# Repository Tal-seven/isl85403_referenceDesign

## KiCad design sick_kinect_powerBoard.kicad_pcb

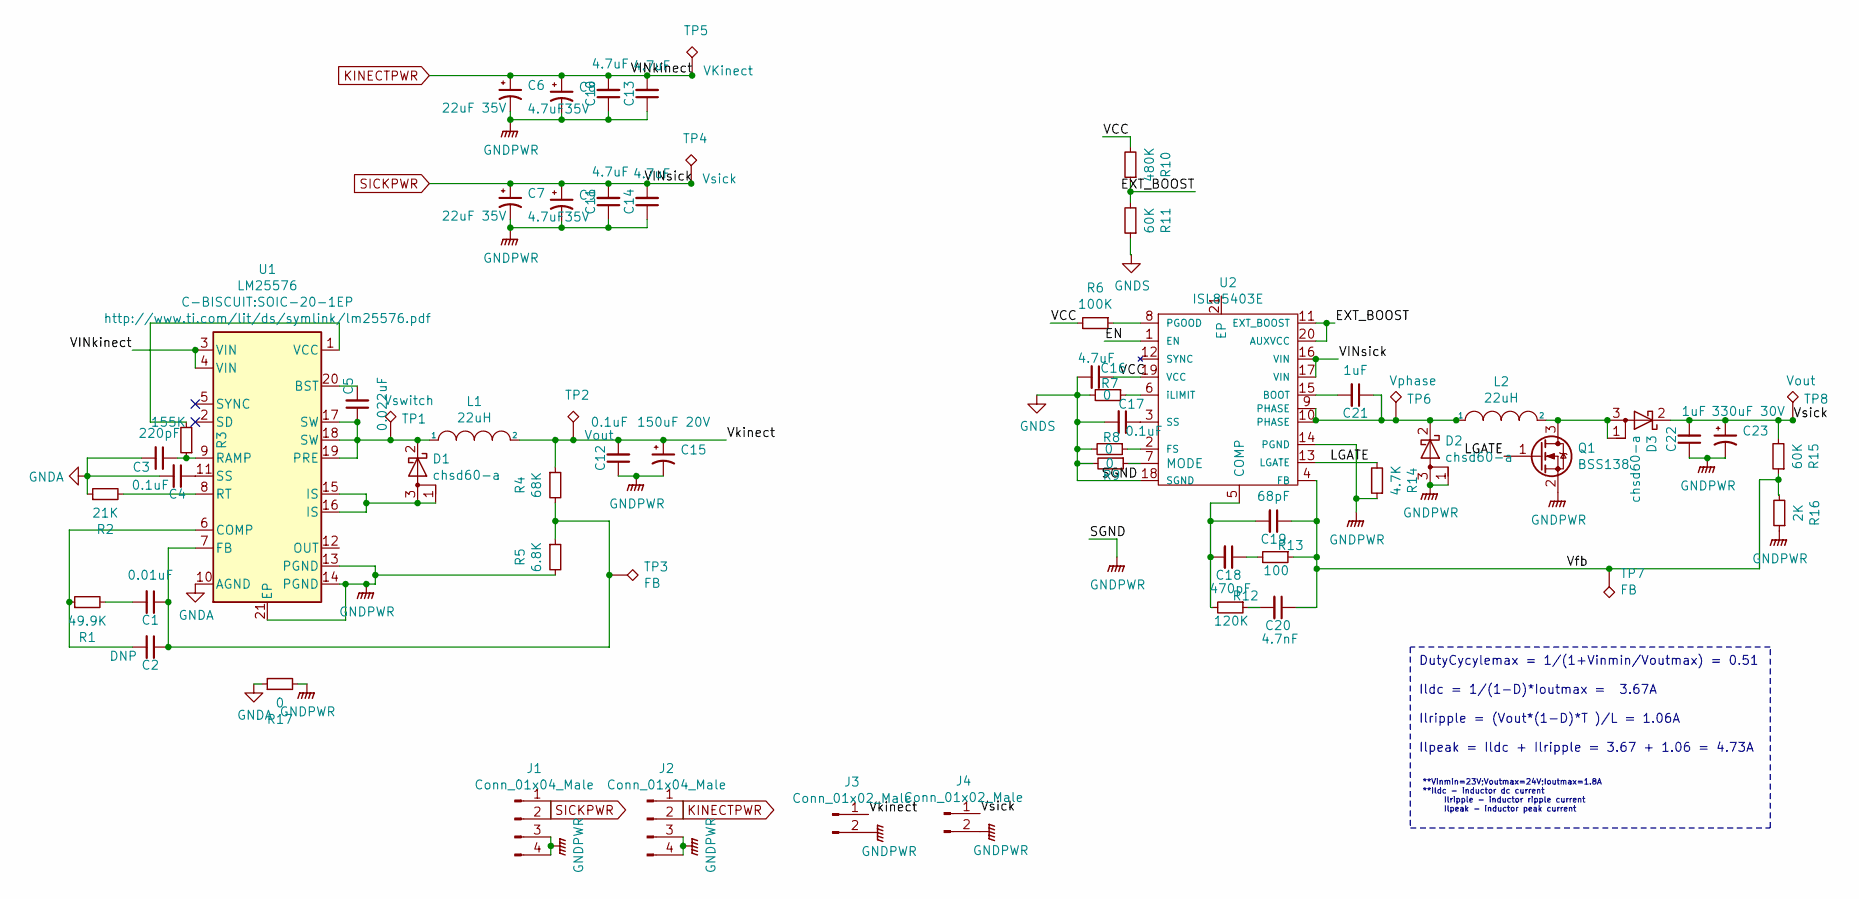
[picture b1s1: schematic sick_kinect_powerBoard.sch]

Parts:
C1: 0.01uF; C_0603_1608Metric_Pad1.05x0.95mm_HandSolder
C2: DNP; C_0603_1608Metric_Pad1.05x0.95mm_HandSolder
C3: 220pF; C_0603_1608Metric_Pad1.05x0.95mm_HandSolder
C4, C12, C17: 0.1uF; C_0603_1608Metric_Pad1.05x0.95mm_HandSolder
C5: 0.022uF; C_0603_1608Metric_Pad1.05x0.95mm_HandSolder
C6, C7: 22uF 35V; CP_Elec_6.3x5.3
C8, C9: 4.7uF35V; CP_Elec_4x5.7
C10, C11, C13, C14, C16: 4.7uF; C_0603_1608Metric_Pad1.05x0.95mm_HandSolder
C15: 150uF 20V; CP_Elec_6.3x7.7
C18: 470pF; C_0603_1608Metric_Pad1.05x0.95mm_HandSolder
C19: 68pF; C_0603_1608Metric_Pad1.05x0.95mm_HandSolder
C20: 4.7nF; C_0603_1608Metric_Pad1.05x0.95mm_HandSolder
C21, C22: 1uF; C_0603_1608Metric_Pad1.05x0.95mm_HandSolder
C23: 330uF 30V; CP_Elec_10x10
D1, D2, D3: chsd60-a; TO-252-2
J1, J2: Conn_01x04_Male; Molex_MegaFit_2x02x5.70mm_Straight
J3, J4: Conn_01x02_Male; Molex_Mega-Fit_76829-0102_2x01_P5.70mm_Vertical
L1, L2: 22uH; L_12x12mm_H4.5mm
Q1: BSS138; SOT-23
R1: 49.9K; R_0603_1608Metric_Pad1.05x0.95mm_HandSolder
R2: 21K; R_0603_1608Metric_Pad1.05x0.95mm_HandSolder
R3: 155K; R_0603_1608Metric_Pad1.05x0.95mm_HandSolder
R4: 68K; R_0603_1608Metric_Pad1.05x0.95mm_HandSolder
R5: 6.8K; R_0603_1608Metric_Pad1.05x0.95mm_HandSolder
R6: 100K; R_0603_1608Metric_Pad1.05x0.95mm_HandSolder
R7, R8, R9, R17: 0; R_0603_1608Metric_Pad1.05x0.95mm_HandSolder
R10: 480K; R_0603_1608Metric_Pad1.05x0.95mm_HandSolder
R11, R15: 60K; R_0603_1608Metric_Pad1.05x0.95mm_HandSolder
R12: 120K; R_0603_1608Metric_Pad1.05x0.95mm_HandSolder
R13: 100; R_0603_1608Metric_Pad1.05x0.95mm_HandSolder
R14: 4.7K; R_0603_1608Metric_Pad1.05x0.95mm_HandSolder
R16: 2K; R_0603_1608Metric_Pad1.05x0.95mm_HandSolder
TP1: Vswitch; TestPoint_Pad_1.5x1.5mm
TP2, TP8: Vout; TestPoint_Pad_1.5x1.5mm
TP3, TP7: FB; TestPoint_Pad_1.5x1.5mm
TP4: Vsick; TestPoint_Pad_1.5x1.5mm
TP5: VKinect; TestPoint_Pad_1.5x1.5mm
TP6: Vphase; TestPoint_Pad_1.5x1.5mm
U1: LM25576; SOIC-20-1EP
U2: ISL85403E; QFN-20-1EP_4x4mm_P0.5mm_EP2.7x2.7mm_ThermalVias

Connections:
/EN: U2.1 (EN)
/EXT_BOOST: R10.1, R11.2, U2.11 (EXT_BOOST), U2.20 (AUXVCC)
/LGATE: Q1.1 (G), R14.2, U2.13 (LGATE)
/VCC: C16.1, R6.2, R10.2, U2.19 (VCC)
/Vfb: C19.1, C20.1, R13.1, R15.1, R16.2, TP7.1, U2.4 (FB)
/Vkinect: C12.2, C15.1, J3.1, L1.2, R4.1, TP2.1
/Vsick: C22.2, C23.1, D3.2 (K), J4.1, R15.2, TP8.1
GNDA: C3.2, C4.2, R2.1, R17.1, U1.10 (AGND)
GNDPWR: C6.2, C7.2, C8.2, C9.2, C10.1, C11.1, C12.1, C13.1, C14.1, C15.2, C16.2, C17.2, C22.1, C23.2, D2.1 (A), D2.3 (A), J1.3, J1.4, J2.3, J2.4, J3.2, J4.2, Q1.2 (S), R5.2, R7.2, R8.2, R9.2, R11.1, R14.1, R16.1, R17.2, U1.13 (PGND), U1.14 (PGND), U1.21 (EP), U2.14 (PGND), U2.18 (SGND)
KINECTPWR: C6.1, C8.1, C10.2, C13.2, J2.1, J2.2, TP5.1, U1.3 (VIN), U1.4 (VIN)
unnamed: C1.1, C2.1, R4.2, R5.1, TP3.1, U1.7 (FB)
unnamed: C1.2, R1.2
unnamed: C2.2, R1.1, U1.6 (COMP)
unnamed: C3.1, R3.1, U1.9 (RAMP)
unnamed: C4.1, U1.11 (SS)
unnamed: C5.1, D1.2 (K), L1.1, TP1.1, U1.17 (SW), U1.18 (SW), U1.19 (PRE)
unnamed: C5.2, U1.20 (BST)
unnamed: C17.1, U2.3 (SS)
unnamed: C18.1, R13.2
unnamed: C18.2, C19.2, R12.2, U2.5 (COMP)
unnamed: C20.2, R12.1
unnamed: C21.1, D2.2 (K), L2.1, TP6.1, U2.9 (PHASE), U2.10 (PHASE)
unnamed: C21.2, U2.15 (BOOT)
unnamed: D1.1 (A), D1.3 (A), U1.15 (IS), U1.16 (IS)
unnamed: D3.1 (A), D3.3 (A), L2.2, Q1.3 (D)
unnamed: R2.2, U1.8 (RT)
unnamed: R3.2, U1.1 (VCC)
unnamed: R6.1, U2.8 (PGOOD)
unnamed: R7.1, U2.6 (iLIMIT)
unnamed: R8.1, U2.2 (FS)
unnamed: R9.1, U2.7 (MODE)
SICKPWR: C7.1, C9.1, C11.2, C14.2, J1.1, J1.2, TP4.1, U2.16 (VIN), U2.17 (VIN)

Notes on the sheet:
DutyCycylemax = 1/(1+Vinmin/Voutmax) = 0.51 Ildc = 1/(1-D)*Ioutmax = 3.67A Ilripple = (Vout*(1-D)*T )/L = 1.06A Ilpeak = Ildc + Ilripple = 3.67 + 1.06 = 4.73A
**Vinmin=23V;Voutmax=24V;Ioutmax=1.8A **Ildc - inductor dc current Ilripple - inductor ripple current Ilpeak - inductor peak current

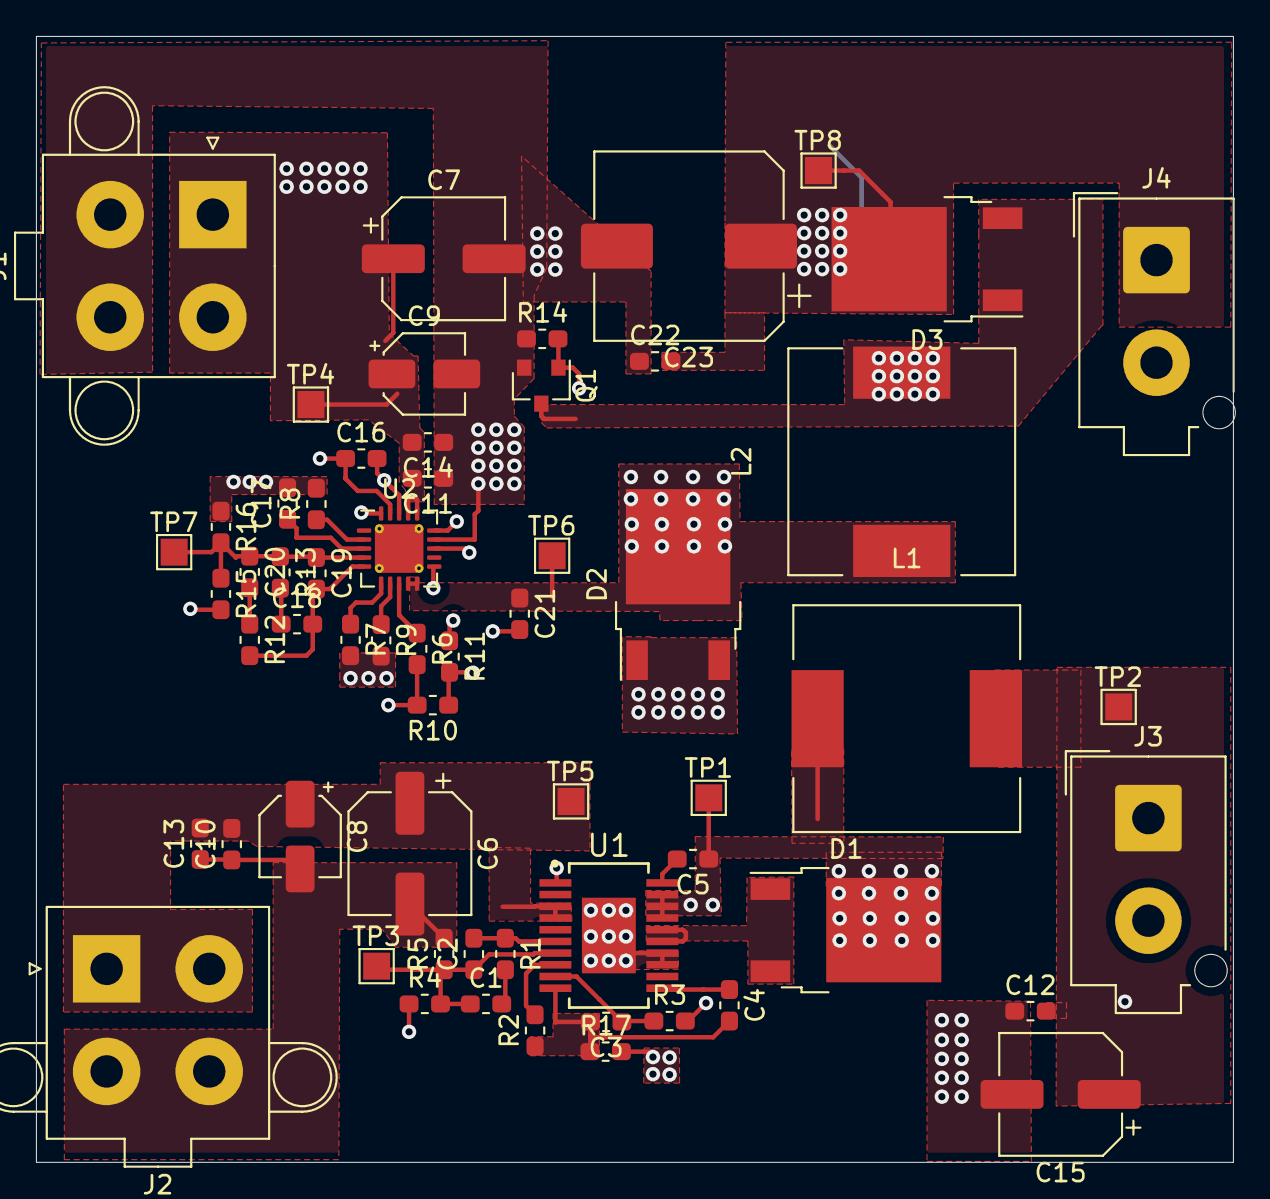
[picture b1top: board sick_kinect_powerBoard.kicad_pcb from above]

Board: 4 copper layers, 66.5 x 62.5 mm, 60 parts (0 on the bottom side), 31 nets.

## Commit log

2019-10-10 file upload
2019-10-10 minor
